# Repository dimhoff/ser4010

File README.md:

SER4010 - UART controllable Si4010 based tunable OOK/FSK RF transmitter
=======================================================================
The SER4010 module is a tunable Sub-GHz RF OOK/FSK transmitter based on the
Silicon Labs Si4010 chip. It is controlled from a PC through standard UART
based serial connection. The encoding of the frames is fully done in software
on the PC, while the actual modulation and sending is offloaded to the module.
This allows for great flexibility in the transmitted signals, while having
accurate signal timing. While having the full programming capacity of a normal
PC platform.

The Si4010 chip can operate in a frequency range of 27 to 960 MHz. Although the
actual frequency band it can effectively operate on depends on the
antenna/matching network. Within its operating band the transmitter can be
tuned to allow matching the receivers frequency, causing better
reception/range.

Hardware connections
--------------------
The SER4010 firmware is controlled using a 3.3 Volt serial(RS-232 like)
connection.

The pins are mapped as follows:

  * VCC   = 3.3 Volt Supply
  * GPIO7 = TX data (connect to RX on remote side)
  * GPIO6 = RX data (connect to TX on remote side)
  * GND   = ground

The following communication parameters are used:

  * bit rate = 9600 Baud
  * Data bits = 8
  * Parity bits = None
  * Stop bits = 1

Suggested is to use a 3.3 volt compatible USB-to-serial adapter, like a FT232
or CP2102. The module can also be directly connected to a RaspberryPi, or
similar.

## SER4010 USB PCB
The hardware/ directory contains a PCB design for a USB connected SER4010
device. This hardware is still under development and is untested testing.

Compiling the SER4010 Firmware
------------------------------
**Note: This is only useful if you plan to develop on the firmware. Else use
the precompiled firmware from GitHub releases section.**

For compiling the SER4010 firmware the Silicon Labs IDE and Si4010 Example
Programs are required. These are both free downloads from the Silabs website.
Note that the Silicon Labs IDE only runs on MS Windows.

First copy some files from the Si4010 Example Programs archive into the SER4010
source:

  * Si4010\_example\_programs/fstep\_demo/src/fstep\_startup.a51 --> ser4010/firmware/ser4010/src/custom\_startup.a51
  * Si4010\_example\_programs/common --> ser4010/firmware/common

Next start the Silicon Labs IDE and open the
ser4010/firmware/ser4010/bin/ser4010.wsp workspace. It should now be possible
to compile the project. This will generate the ser4010.hex firmware file in the
ser4010/firmware/ser4010/out/ directory.

Compiling the Software
----------------------
Run the following to compile the libser4010 library and tools:

    # cd build
    # cmake ../
    # make

The software uses /dev/ttyUSB0 by default as serial port. If your module is
connected to a different serial port you can change the default serial device
to use by using the following cmake command instead of the above one:

    # cmake ../ -DDEFAULT_SERIAL_DEV=<your serial port>

For example for the Raspberry PI use '/dev/ttyAMA0' when the module is connected
to the internal serial port.

Loading the Firmware
--------------------
TODO: Extend chapter...

You have to load the SER4010 firmware into the Si4010 module. Either by
programming it once into the non-volatile NVM memory. Or by loading it after
every reboot into the modules RAM.

See the [si4010prog tool](https://github.com/dimhoff/si4010prog)

Serial port configuration
-------------------------
Make sure the serial port to which the module is connected does not have a
serial console or any other software using it. Else the communication will get
scrambled.

Note that the Raspberry PI 1/2 have a bootloader that always outputs a string
to the internal serial port at boot. This causes a communication-out-of-sync
error the first time you run any of the ser4010 tools. Just try again.

To use the internal serial port of the Raspberry PI 3 you must disable the
Bleutooth. This can be done using the pi3-disable-bt Device tree overlay.

Using the Software
------------------
All SER4010 tools provide a '-d' option to specify which serial port to use.
This option is only needed if you didn't specify the correct serial port at
compile time, see *Compiling the Software*, or when using multiple modules.
Valid arguments for the '-d' option are for example /dev/ttyS0, /dev/ttyUSB0 or
/dev/ttyAMA0.

To test if the communication with the module works you can use the
ser4010_test_comm utility from the tools/ directory. An example of a working
module output:

    # build/tools/ser4010_test_comm
    Communication OK

The tool will either output 'Communication OK' or an error. In case of error
verify you properly connected the device (switched TX/RX?). And verify you are
using the correct serial port and no other software is using the serial port.

## ser4010_dump
The ser4010_dump tool can be used to dump the current module configuration.
This is mainly for debugging. You don't have to manual change any of these
configuration parameters since all other SER4010 tools will automatically chose
the correct parameters for there application.

Example output:

    # build/tools/ser4010_dump
    Device Info:
    ------------
    Device Type: 0x0100
    Device Revision: 3
    
    ODS settings:
    ------------
    bModulationType: OOK (0)
    bClkDiv: 5
    bEdgeRate: 0
    bGroupWidth: 6
    wBitRate: 1100
    bLcWarmInt: 8
    bDivWarmInt: 5
    bPaWarmInt: 4
    
    PA settings:
    ------------
    fAlpha: 0.000000
    fBeta: 0.000000
    bLevel: 60
    bMaxDrv: 0
    wNominalCap: 256
    
    Encoder settings:
    ------------
    Encoding: None/NRZ (0)
    
    Freq settings:
    ------------
    frequency: 433900000.000000
    freq. deviation: 104

## ser4010_somfy
TODO:

## ser4010_kaku
TODO:

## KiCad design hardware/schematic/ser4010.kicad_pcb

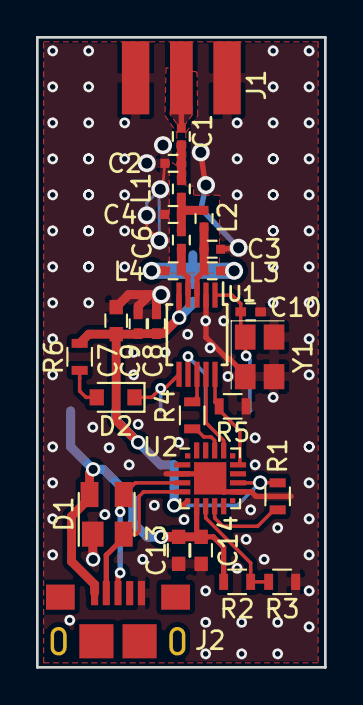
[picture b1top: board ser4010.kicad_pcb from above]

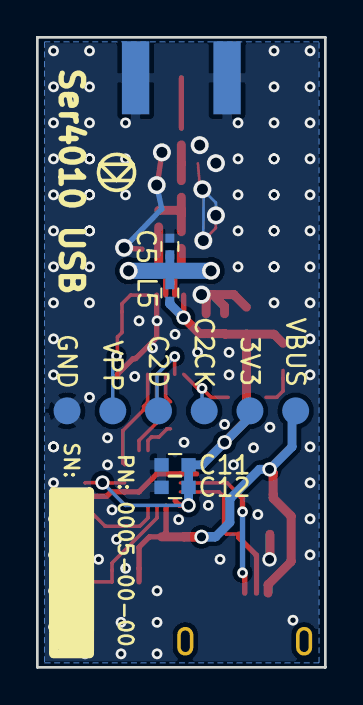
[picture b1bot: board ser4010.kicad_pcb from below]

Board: 2 copper layers, 16.0 x 35.0 mm, 38 parts (10 on the bottom side), 21 nets.

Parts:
C1, C9: 270pF; C_0402
C2, C4: 6.8pF; C_0402
C3: 4.3pF; C_0402
C5: 2.7pF; C_0402
C6: 1.8pF; C_0402
C7: 2.2uF; C_0603
C8: 1nF; C_0402
C10: 5pF; C_0402
C11, C13: 4.7uF; C_0603
C12, C14: 0.1uF; C_0603
D1: SP0503BAHT; SOT-143
D2: LED; D_0805
J1: Conn_Coaxial; Adafruit-SMA_EDGELAUNCH
J2: USB_OTG; Amphenal_FCI_10118193-0001LF_USB_Micro-B
J3: 3V3; Measurement_Point_Round-SMD-Pad_Small-Labeled
J4: VPP; Measurement_Point_Round-SMD-Pad_Small-Labeled
J5: C2CK; Measurement_Point_Round-SMD-Pad_Small-Labeled
J6: C2D; Measurement_Point_Round-SMD-Pad_Small-Labeled
J7: GND; Measurement_Point_Round-SMD-Pad_Small-Labeled
J8: VBUS; Measurement_Point_Round-SMD-Pad_Small-Labeled
L1: 18nH; C_0402
L2: 56nH; C_0402
L3, L4: 16nH; C_0402
L5: 220nH; C_0402
R1: 1k; R_0603
R2: 22.1k; R_0603
R3: 47.5k; R_0603
R4: 100; R_0603
R5: DNF; R_0603
R6: 470; R_0603
U1: Si4010-GT; MSOP-10_3x3mm_Pitch0.5mm
U2: CP2102N-A01-GQFN20; SiliconLabs_QFN-20-1EP_3x3mm_Pitch0.5mm
Y1: LFXTAL055915; Crystal_SMD_IQD_CFPX-180_4pin_3.2x2.5mm

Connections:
+3V3: C7.1, C8.1, C9.1, C11.1, C12.1, J3.1, L5.1, R1.1, R6.2, U1.5, U2.6, U2.13
/D+: D1.3, J2.3, U2.4
/D-: D1.2, J2.2, U2.5
/VBUS: C13.1, C14.1, D1.4, J2.1, J8.1, R2.1, U2.7
GND: C2.2, C3.2, C4.2, C5.1, C7.2, C8.2, C9.2, C10.1, C11.2, C12.2, C13.2, C14.2, D1.1, J1.2, J2.5, J7.1, R3.2, R5.1, U1.2, U2.3, U2.12, U2.21, Y1.2, Y1.3, Y1.4
unnamed: C1.1, C2.1, L1.2
unnamed: C1.2, J1.1
unnamed: C3.1, L2.1, L3.1, U1.3
unnamed: C4.1, C6.2, L1.1, L2.2
unnamed: C5.2, L3.2, L4.1, L5.2
unnamed: C6.1, L4.2, U1.4
unnamed: C10.2, J4.1, U1.1, Y1.1
unnamed: D2.1, J5.1, U1.6
unnamed: D2.2, R6.1
unnamed: J6.1, U1.7
unnamed: R1.2, U2.9
unnamed: R2.2, R3.1, U2.8
unnamed: R4.1, U1.8
unnamed: R4.2, U2.18
unnamed: R5.2, U1.10, U2.15
unnamed: U1.9, U2.17

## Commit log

2014-10-19 Add information about firmware compiling to README.md
2014-11-07 Replace 'if else' construction with switch case
2014-11-07 White space fixes; no code changes
2014-11-07 Split protocol defines into seperate header file just as in libser4010
2014-11-07 Default to error if no result code is set
2014-11-07 Allow setting data encoding on Si4010
2014-11-08 Added device type and revision to identify firmware
2014-11-08 Display encoding in ser4010_dump
2014-11-12 Automatically apply RF configuration, removed ser4010_reconfigure()
2014-11-12 Fix type, name and default value of FSK freq. deviation
2014-11-12 Added ser4010_config() high level configuration API function
2014-11-15 Added ser4010_si443x tool
2014-11-22 Fix default bit rate value in usage() output
2014-11-22 Fix frequency deviation option input validation
2015-01-01 Extended README
2015-04-19 Make default serial device a build option
2015-09-16 blindctl_somfy: Improved documentation of arguments
2015-09-16 blindctl_somfy: Stricter argument checking
2016-04-09 Added NEWS file
2016-04-11 Updated email address
2016-04-11 Rename tools to uniform names
    Renamed:
    blindctl_somfy -> ser4010_somfy
    test_comm -> ser4010_test_comm
2016-04-11 ser4010_somfy: change '-D' option to '-d'
    Bring option inline with other tools
2016-04-11 ser4010_test_comm: Add user output
2016-06-26 Extended README.md
2016-07-03 Append to CMAKE_C_FLAGS instead of overwriting them
    Thanks to Manuel Coenen for pointing this out.
2018-08-08 Make befloattoh() and htobefloat() functions static
    This fixes compilation errors
2018-08-11 FW: Replace magic number by define
2018-08-11 libser4010: Try to recover from out-of-sync communication
    If a command time outs because it takes very long, libser4010 will
    return an error to the calling program. However if the ser4010 command
    does succeed after the timeout, it will still return a result packet.
    This packet is stored in the OS receive buffer. The next time a command
    is send to the ser4010 device, libser4010 will directly read the
    previous response from the OS buffer. libser4010 would detect this
2018-08-11 KAKU: Increase PA power level
2018-08-11 Replace space identation with tabs
    No functional change
2018-08-11 Fix signed/unsigned comparison
2018-08-11 Enable '-Wextra' warnings
2018-08-11 Remove redundant dehexify() implementation
2018-08-11 Add some range checks on ser4010_config() data rate and fix FPE
    The data rate range was not checked and could go out of range, using
    16-bit instead of 15-bit. Also a wBitRate of zero caused a floating
    point exception. Fixed this by checking for zero.
2018-08-29 HW: Added initial Ser4010 PCB design
2018-08-29 LIB: extend documentation in header file
2018-08-29 Tools: added ser4010_console utility
    Mainly for testing
2018-08-29 HW: Switch to di_kicad_library repository for KiCad libs
2018-08-29 HW: fix DI Logo orientation
2018-08-29 Add info about SER4010-USB PCB in README.md
2018-08-29 HW: add gitignore files for KiCad files and datasheets
2018-08-29 HW: Use updated Si4010-GT symbol
2018-09-15 HW: fix project number
2019-02-27 HW: add part information
2019-02-27 SW: Add some more tools for testing
    These tools are meant for testing only!
2019-02-27 Remove partial tool: ser4010_smartwares

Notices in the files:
hardware/schematic/ser4010.kicad_pcb:
Copyright (c) 2018, David Imhoff
License: BSD-3-Clause
